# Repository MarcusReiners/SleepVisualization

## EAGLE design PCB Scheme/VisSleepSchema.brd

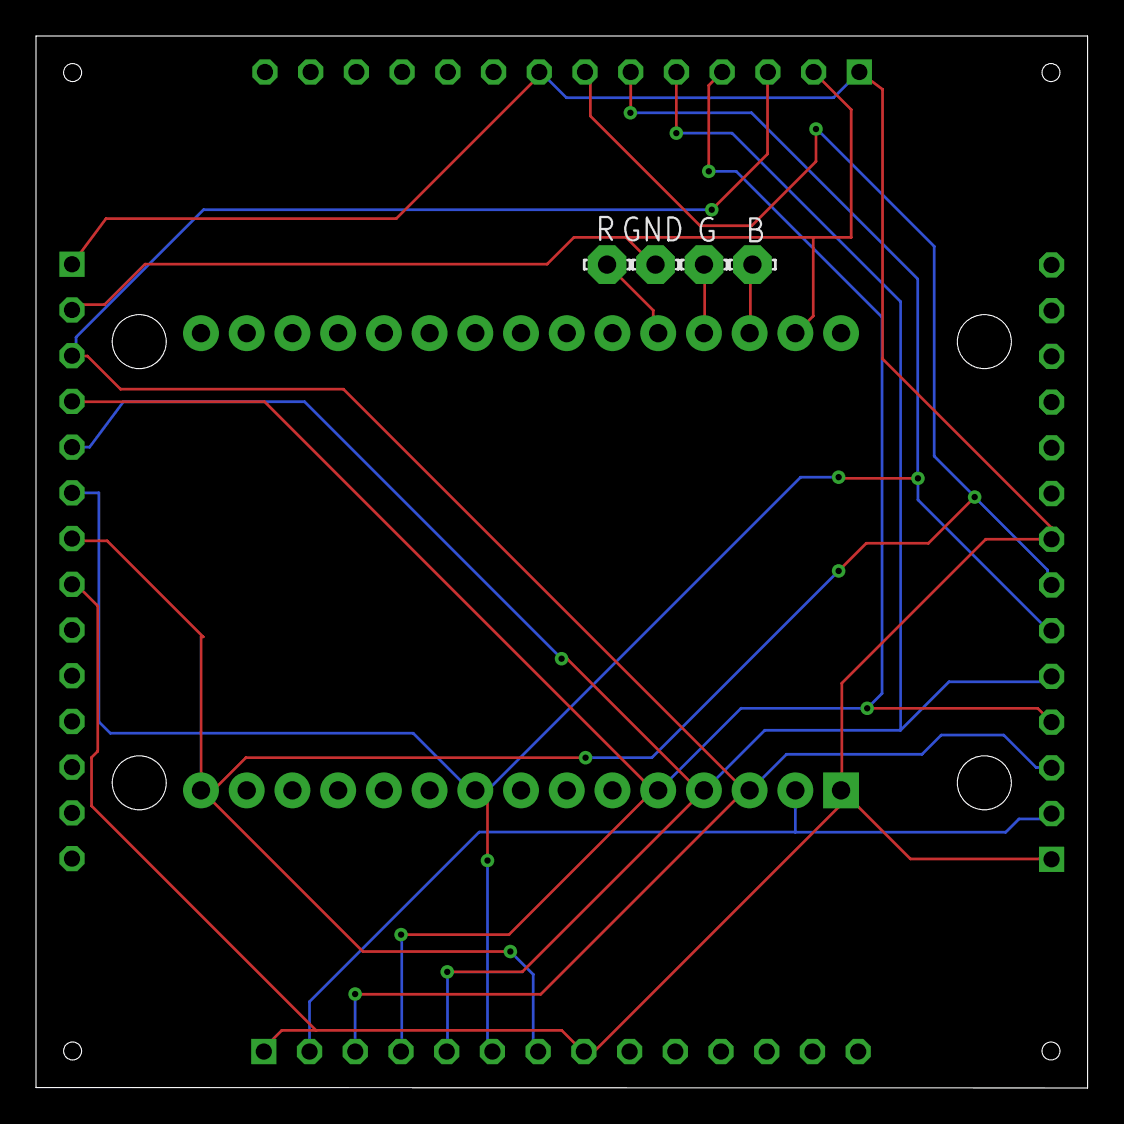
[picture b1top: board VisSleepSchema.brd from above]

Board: 2 copper layers, 58.4 x 58.4 mm, 9 parts (1 on the bottom side), 11 nets.

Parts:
A1, A2, A3, A4: TFT; 2.8_LCD
B: LSP10
G: LSP10
GND: LSP10
R: LSP10
U1: ESP32-DEVKIT-V1; MODULE_ESP32_DEVKIT_V1

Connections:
unnamed: A1.1, A1.8, A2.1, A2.8, A3.1, A3.8, A4.1, A4.8, U1.1
unnamed: A2.2, A3.2, GND.MP, U1.29
unnamed: A1.3, A2.3, A3.3, A4.3, U1.3
unnamed: B.MP, U1.28
unnamed: G.MP, U1.27
unnamed: A1.4, A2.4, A3.4, A4.4, U1.5
unnamed: A1.5, A2.5, A3.5, A4.5, U1.4
unnamed: A1.6, A2.6, A3.6, A4.6, U1.9
unnamed: A1.7, A2.7, A3.7, A4.7, U1.15
unnamed: R.MP, U1.26
S$2: A4.2, U1.2

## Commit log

2023-06-27 Update on Overleaf.
2023-07-11 Erstellt mit Colaboratory
2023-07-21 add Flutter code
2023-07-22 Add firebase service and device ID generator
2023-10-27 update2
2023-10-27 add documentation
2023-11-17 add config
